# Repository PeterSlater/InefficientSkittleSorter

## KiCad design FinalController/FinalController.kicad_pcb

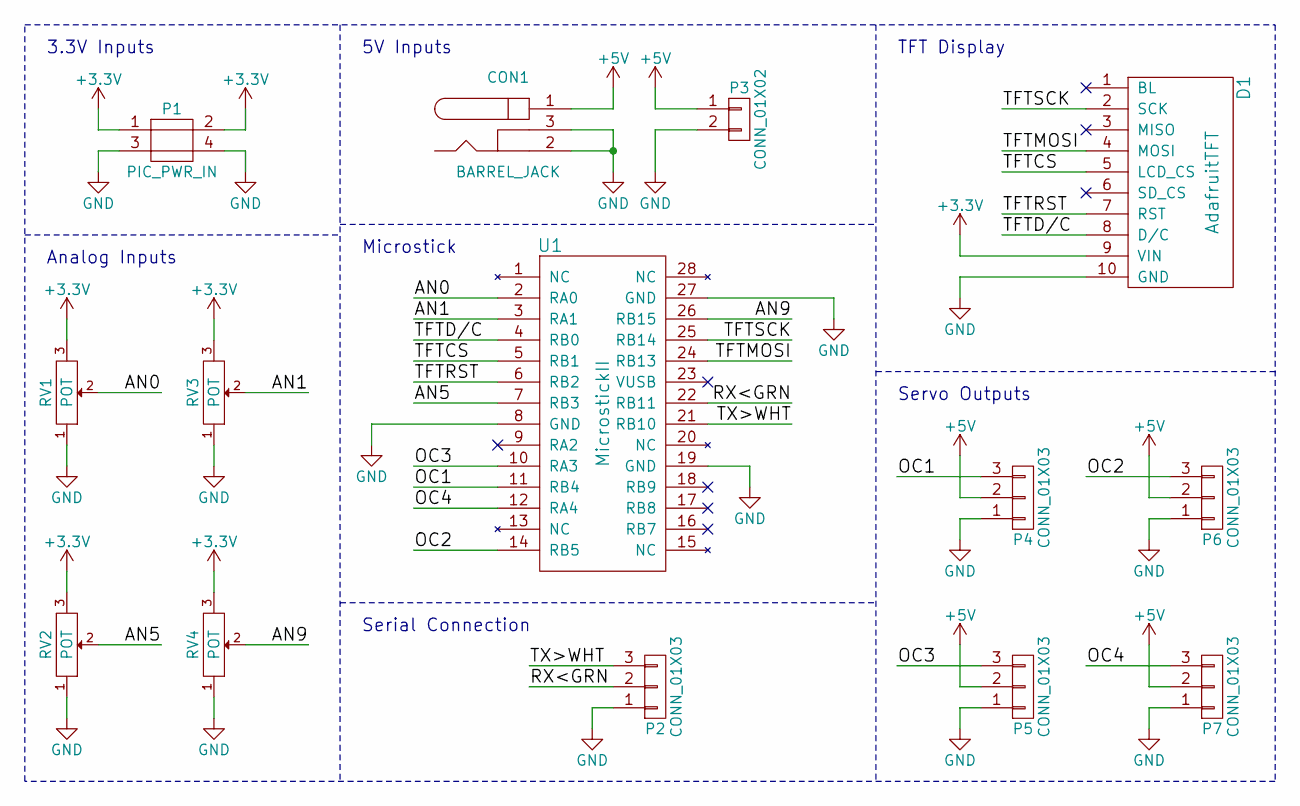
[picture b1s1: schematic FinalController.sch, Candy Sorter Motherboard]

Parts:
CON1: BARREL_JACK
D1: AdafruitTFT
P1: PIC_PWR_IN; Pin_Header_Straight_2x02
P2, P4, P5, P6, P7: CONN_01X03; Pin_Header_Straight_1x03
P3: CONN_01X02; TerminalBlock_Pheonix_MKDS1.5-2pol
RV1, RV2, RV3, RV4: POT; Potentiometer_Trimmer-Suntan-TSR-3386P
U1: MicrostickII

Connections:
+3V3: D1.9 (VIN), P1.1, P1.2, RV1.3, RV2.3, RV3.3, RV4.3
+5V: CON1.1, P3.1, P4.2, P5.2, P6.2, P7.2
/AN0: RV1.2, U1.2 (RA0)
/AN1: RV3.2, U1.3 (RA1)
/AN5: RV2.2, U1.7 (RB3)
/AN9: RV4.2, U1.26 (RB15)
/OC1: P4.3, U1.11 (RB4)
/OC2: P6.3, U1.14 (RB5)
/OC3: P5.3, U1.10 (RA3)
/OC4: P7.3, U1.12 (RA4)
/RX<GRN: P2.2, U1.22 (RB11)
/TFTCS: D1.5 (LCD_CS), U1.5 (RB1)
/TFTD/C: D1.8 (D/C), U1.4 (RB0)
/TFTMOSI: D1.4 (MOSI), U1.24 (RB13)
/TFTRST: D1.7 (RST), U1.6 (RB2)
/TFTSCK: D1.2 (SCK), U1.25 (RB14)
/TX>WHT: P2.3, U1.21 (RB10)
GND: CON1.2, CON1.3, D1.10 (GND), P1.3, P1.4, P2.1, P3.2, P4.1, P5.1, P6.1, P7.1, RV1.1, RV2.1, RV3.1, RV4.1, U1.8 (GND), U1.19 (GND), U1.27 (GND)

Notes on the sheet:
Analog Inputs
3.3V Inputs
5V Inputs
Microstick
Serial Connection
TFT Display
Servo Outputs

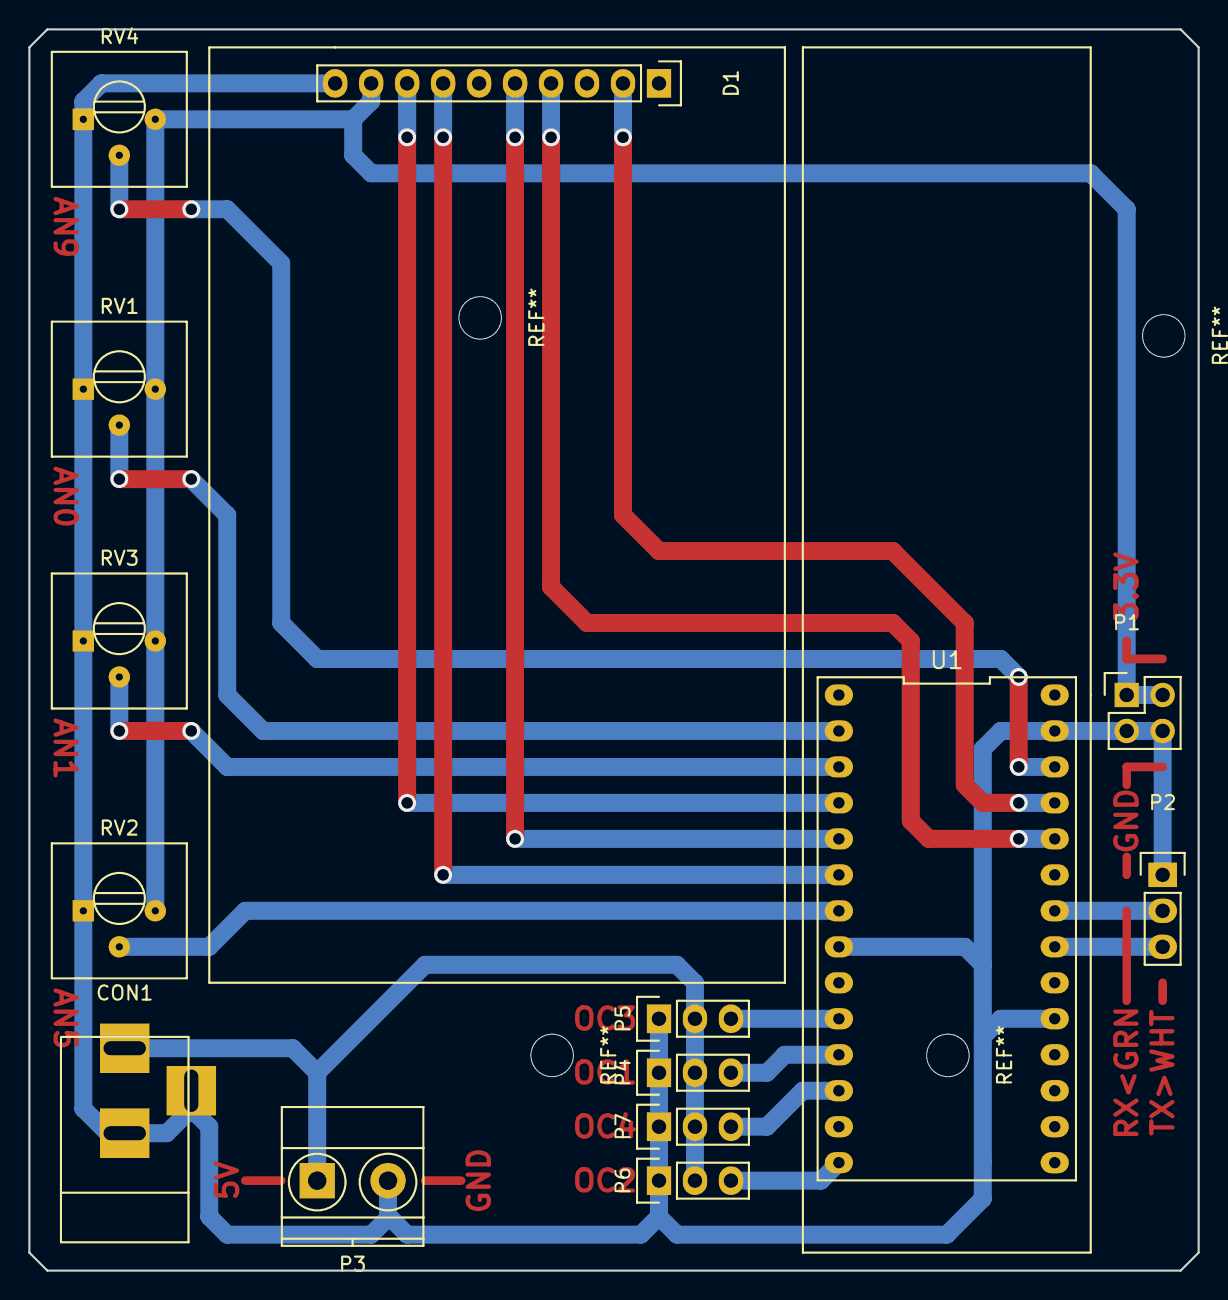
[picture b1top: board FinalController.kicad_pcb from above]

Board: 2 copper layers, 82.5 x 87.6 mm, 14 parts (0 on the bottom side), 18 nets.

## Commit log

2016-11-17 adding camera code with FSM
2016-11-17 adding IK files
2016-11-17 got base to work
2016-11-21 xyz movement roughly working but not coordinate accuracy
2016-12-02 got the camera to detect claw postiion and skittle position
2016-12-02 can see red and get delta X,Y. Need to update FSM to update live X,Y data and more states
2016-12-03 detect FSM working robustly with live update and handles multiple red obj. Median filter positions
2016-12-05 2 color sort demo working
2016-12-08 final version of the code that was demoed.
2016-12-08 Finished design
